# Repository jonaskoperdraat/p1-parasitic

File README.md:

# p1-parasitic
Project with the goal to build a wifi and/or BLE enabled P1-gateway

## P1-gateway

I have a smart meter and want to be able to access readings from it in a (near) realtime fashion. 

## Parasitic

I currently don't have an additional power outlet near the meter so a parasitic device, running of the power supplied by the P1 port would be preferable.

The power supplied by the P1 port is limited, so that is something to take into account.

## ESP32 / M5stick

I have a M5stick laying around with which I've managed to read from the P1 port and post to an MQTT topic before. This also has the benefit of having a battery which might be used as a buffer to supply current for the peak power required to send data over WiFi, whilst charging off the P1 power supply when the M5stick is dormant.

## Smart meter

The meter in my home is a ISKRA AM550-TD2 3-phase meter.

### P1 port

I have confirmed that the P1 port has a 5V power supply on pin #1 and #6.

:question: will the P1 port be able to supply enough power to charge the battery of the M5stick
:question: how much current can the P1 supply?
:question: how much current is required to get the M5stick to charge it's internal battery?

As I don't have the equipment at hand, nor the knowledge to test the max current the P1 port can supply, I will have to find out empirically whether or not the P1 port and the M5stick are a good match.

#### Charging the M5stick

The M5stick has a 80mAh battery and is configured by default to charge at 100mA.

Even though elsewhere a max current draw of 100mA is mentioned [^1] for DSMR 4.x, and no voltage on pins #1 and #2 for the ISKRA AM550, [^1] also mentions that the ISKRA AM550 uses ESMR5.0, which is supposed to be able to output 250mA of current.
I haven't been able to find a spec for ESMR5.0, but [ref/DSMRv5.0.pdf] is a spec for "DSMR5.0 (Dutch Smart Meter Requirements)" which metions a max output of 250mA. The device itself has a label on it with "SMR 5.0", so I'm hoping ESMRv5.0 and DSMRv5.0 are kinda the same thing and the meter will just supply 250mA.

This might even be enough to not have to worry too much about deep sleep...

##### Test setup
Let's see if this configuration will run the M5Stick-C

```
            5V< ───────────┐
            3V3            └──────────── #1 +5V Power supply
            BAT                          #2 Data request
 M5STICK-C  G06                          #3 Data GND         P1
            G36                          #4 -
            G26                          #5 Data line - Open collector
            5V>            ┌──────────── #6 Power GND
            GND ───────────┘
```

In order to test whether the M5stick can operate off of the M5stick, without worrying about reading the telegrams yet, I'll run the following test:

* Attempt to power the M5Stick-C through above cirquit
* Run the M5Stick-C with the following program:
    * On wake up:
        * Connect to WiFi
        * Connect to MQTT
        * publish battery stats to MQTT topic
        * Go to sleep for 10 seconds
* See how long the device lasts. Without power supply, this program can run roughly 3.5 hours.

The P1 port supplies enough power for the M5Stick to run for a prolonged period. The current setup has been
with putting the M5Stick into deep sleep and waking every 10s to connect to WiFi, MQTT, read the P1 data and
publish to MQTT.

## Implementation

I've thought about a number of 'clever' ways to wait for telegrams and to go into deep sleep mode in between.
Like being woken by a timer, or by incoming telegrams. This was mostly motivated by the thought that the P1
port would only supply enough power to charge whilst in deep sleep, and not for sending. However, these 
methods add complexity and might not even be needed, seeing as the P1 port is supposed to be able to provide
250mA.

So I'm starting out (relatively) simple.

> * Connect to WiFi
> * Connect to MQTT
> * Wait for telegram
>   * Upon receiving telegram, send to MQTT \
>     Each telegram will be converted into a JSON message and sent as a single message to MQTT.
>     This can be done using [this library](https://github.com/matthijskooijman/arduino-dsmr)
>   * Wait for next telegram
>
> Display:
>   * WiFi status
>   * MQTT status
>   * \# telegrams received
>   * \# telegrams sent to MQTT
>
> Connection mechanism:
> * Whenever WiFi is disconnected
>   * Attempt to connect
>       * If unsuccessfull, wait _d_ seconds \
>         _d_ being determined by number of attempts, _n_ made so far:
>         | *n* | 1  | 2  | 3  | 4+ |
>         | --- | -: | -: | -: | -: |
>         | ***d*** | 5  | 10 | 30 | 60 |
>       * If successful, reset _n_.
> * Whenever MQTT is disconnected, follow the same schema for connecting to WiFi,
>   *only if* WiFi is connected. Otherwise, do nothing.

## Notes

The M5stickC suffers from a bug where uploading times out. This can be remidied by either shorting `G0` to `GND` while programming using a dupont line, or by updating the firmware if you're brave enough [^2].
update: I've updated the firmware, ridding the device of said bug.

## Log

**17 feb 2021, 11:55**

Just connecting the M5stick to the P1 port using above schema does not show any voltage reported on `v_5vin` or current on `i_5vin`.

:question: Perhaps there's a hardware or configuration adjustment needs to be done before this can be used? 
:question:Or the P1 port might not be able to supply the requested current? 

**17 feb 2021, 17:00**

Apparently I just had +5V and GND mixed up. Sorting this out runs the M5stick just fine.

**19 feb**

I've created the [electronics design](hardware/readme.md) on a breadboard. This turned out to work and I was able
to read P1 messages coming from the meter.

**20 feb** 

I've converted the electronics design from breadboard to prototype PCB as well as designed an [enclosure](hardware/casing).
The M5Stick has been running fine in the 10s sleep/measure cycle. 

## References

[^1] Domoticx Knowledge Center - P1 poort slimme meter (hardware)
[^2] (M5StickC/ATOM on MacOS Catalina can't upload/ ESP32: Timed out waiting for packet header solution (Solved)

[^1]: http://domoticx.com/p1-poort-slimme-meter-hardware/
[^2]: https://forum.m5stack.com/topic/1591/m5stickc-atom-on-macos-catalina-can-t-upload-esp32-timed-out-waiting-for-packet-header-solution-solved

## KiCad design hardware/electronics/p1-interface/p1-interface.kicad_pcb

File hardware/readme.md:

# Hardware

This page should treat any hardware considerations that where made.

## Electronics

The software library I intend to use for reading the P1 telegrams, supports switching the data request line
through a GPIO pin. 

Also, the data signal needs to be inverted and converted to 3.3V. This schema does that:

*note*: the `JP1` connector is number in reverse. This was my way of orienting the connector the right way
on the PCB.

## Casing

I designed a case that will allow me to mount the case to the meter housing and still give me easy access 
to the M5Stick when needed.

The fusion 360 design can be found here: https://a360.co/3IbdbrX

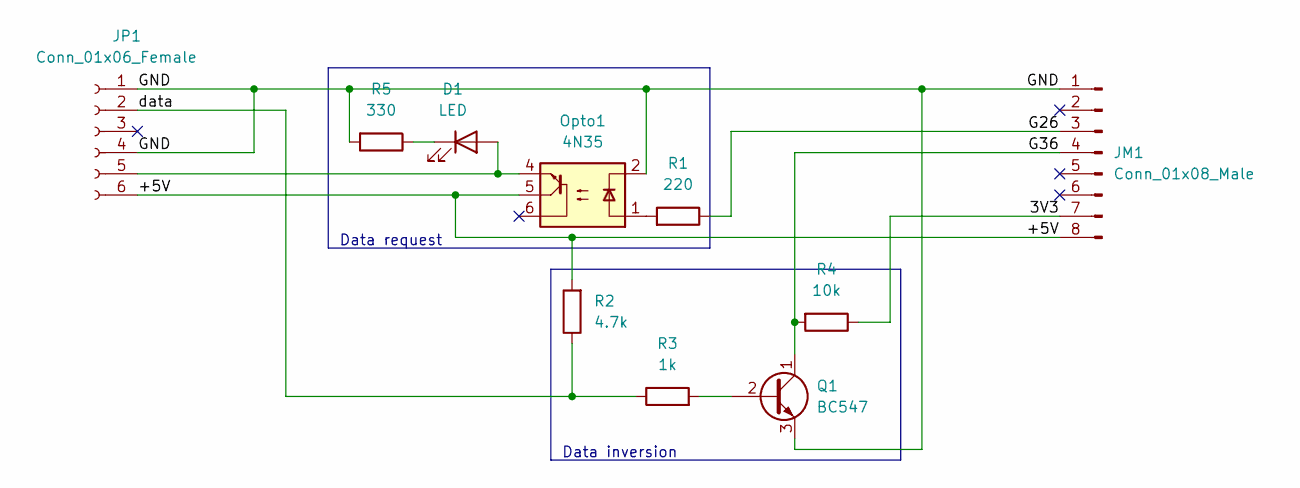
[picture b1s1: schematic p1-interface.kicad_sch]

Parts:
D1: LED; LED_D5.0mm
JM1: Conn_01x08_Male; PinHeader_1x08_P2.54mm_Horizontal
JP1: Conn_01x06_Female; PinHeader_1x06_P2.54mm_Horizontal
Opto1: 4N35; DIP-6_W7.62mm
Q1: BC547; TO-92_Inline_Wide
R1: 220; R_Axial_DIN0207_L6.3mm_D2.5mm_P10.16mm_Horizontal
R2: 4.7k; R_Axial_DIN0207_L6.3mm_D2.5mm_P10.16mm_Horizontal
R3: 1k; R_Axial_DIN0207_L6.3mm_D2.5mm_P10.16mm_Horizontal
R4: 10k; R_Axial_DIN0207_L6.3mm_D2.5mm_P10.16mm_Horizontal
R5: 330; R_Axial_DIN0207_L6.3mm_D2.5mm_P10.16mm_Horizontal

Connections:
/3V3: JM1.7, R4.1
/+5V: JM1.8, JP1.6, Opto1.5, R2.2
/G26: JM1.3, R1.1
/G36: JM1.4, Q1.1 (C), R4.2
/GND: JM1.1, JP1.1, JP1.4, Opto1.2, Q1.3 (E), R5.2
/data: JP1.2, R2.1, R3.1
unnamed: D1.1 (K), R5.1
unnamed: D1.2 (A), JP1.5, Opto1.4
unnamed: Q1.2 (B), R3.2
unnamed: Opto1.1, R1.2

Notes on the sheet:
Data request
Data inversion

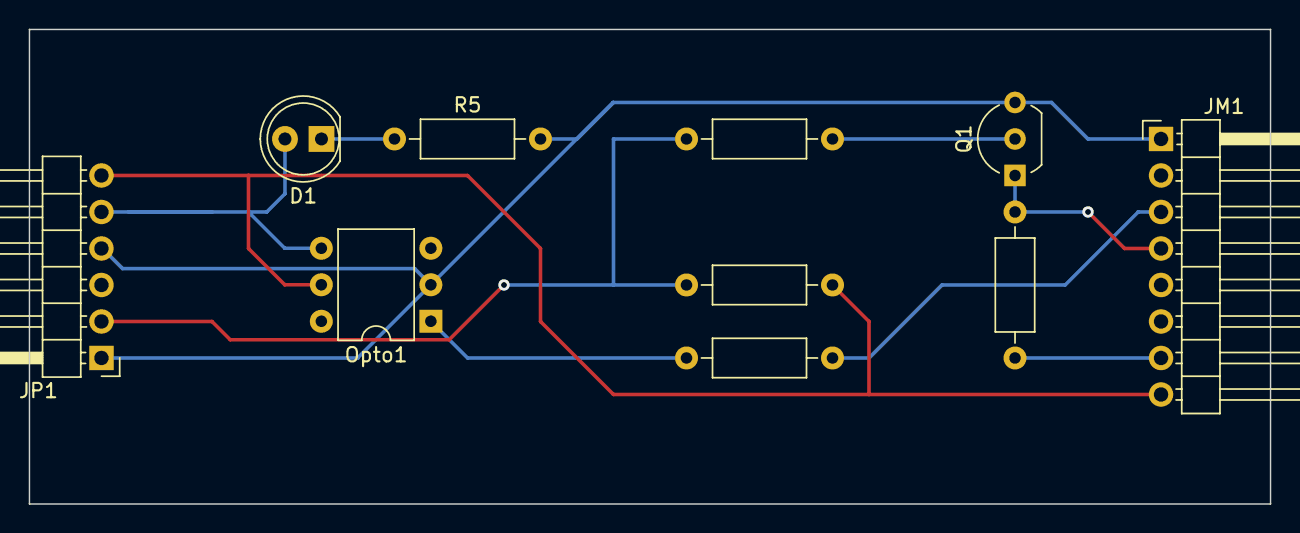
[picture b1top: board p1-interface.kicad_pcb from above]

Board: 2 copper layers, 86.4 x 33.0 mm, 10 parts (0 on the bottom side), 10 nets.

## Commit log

2022-02-19 Add initial implementation idea to readme.md
2022-02-22 Add PCB and enclosure design
